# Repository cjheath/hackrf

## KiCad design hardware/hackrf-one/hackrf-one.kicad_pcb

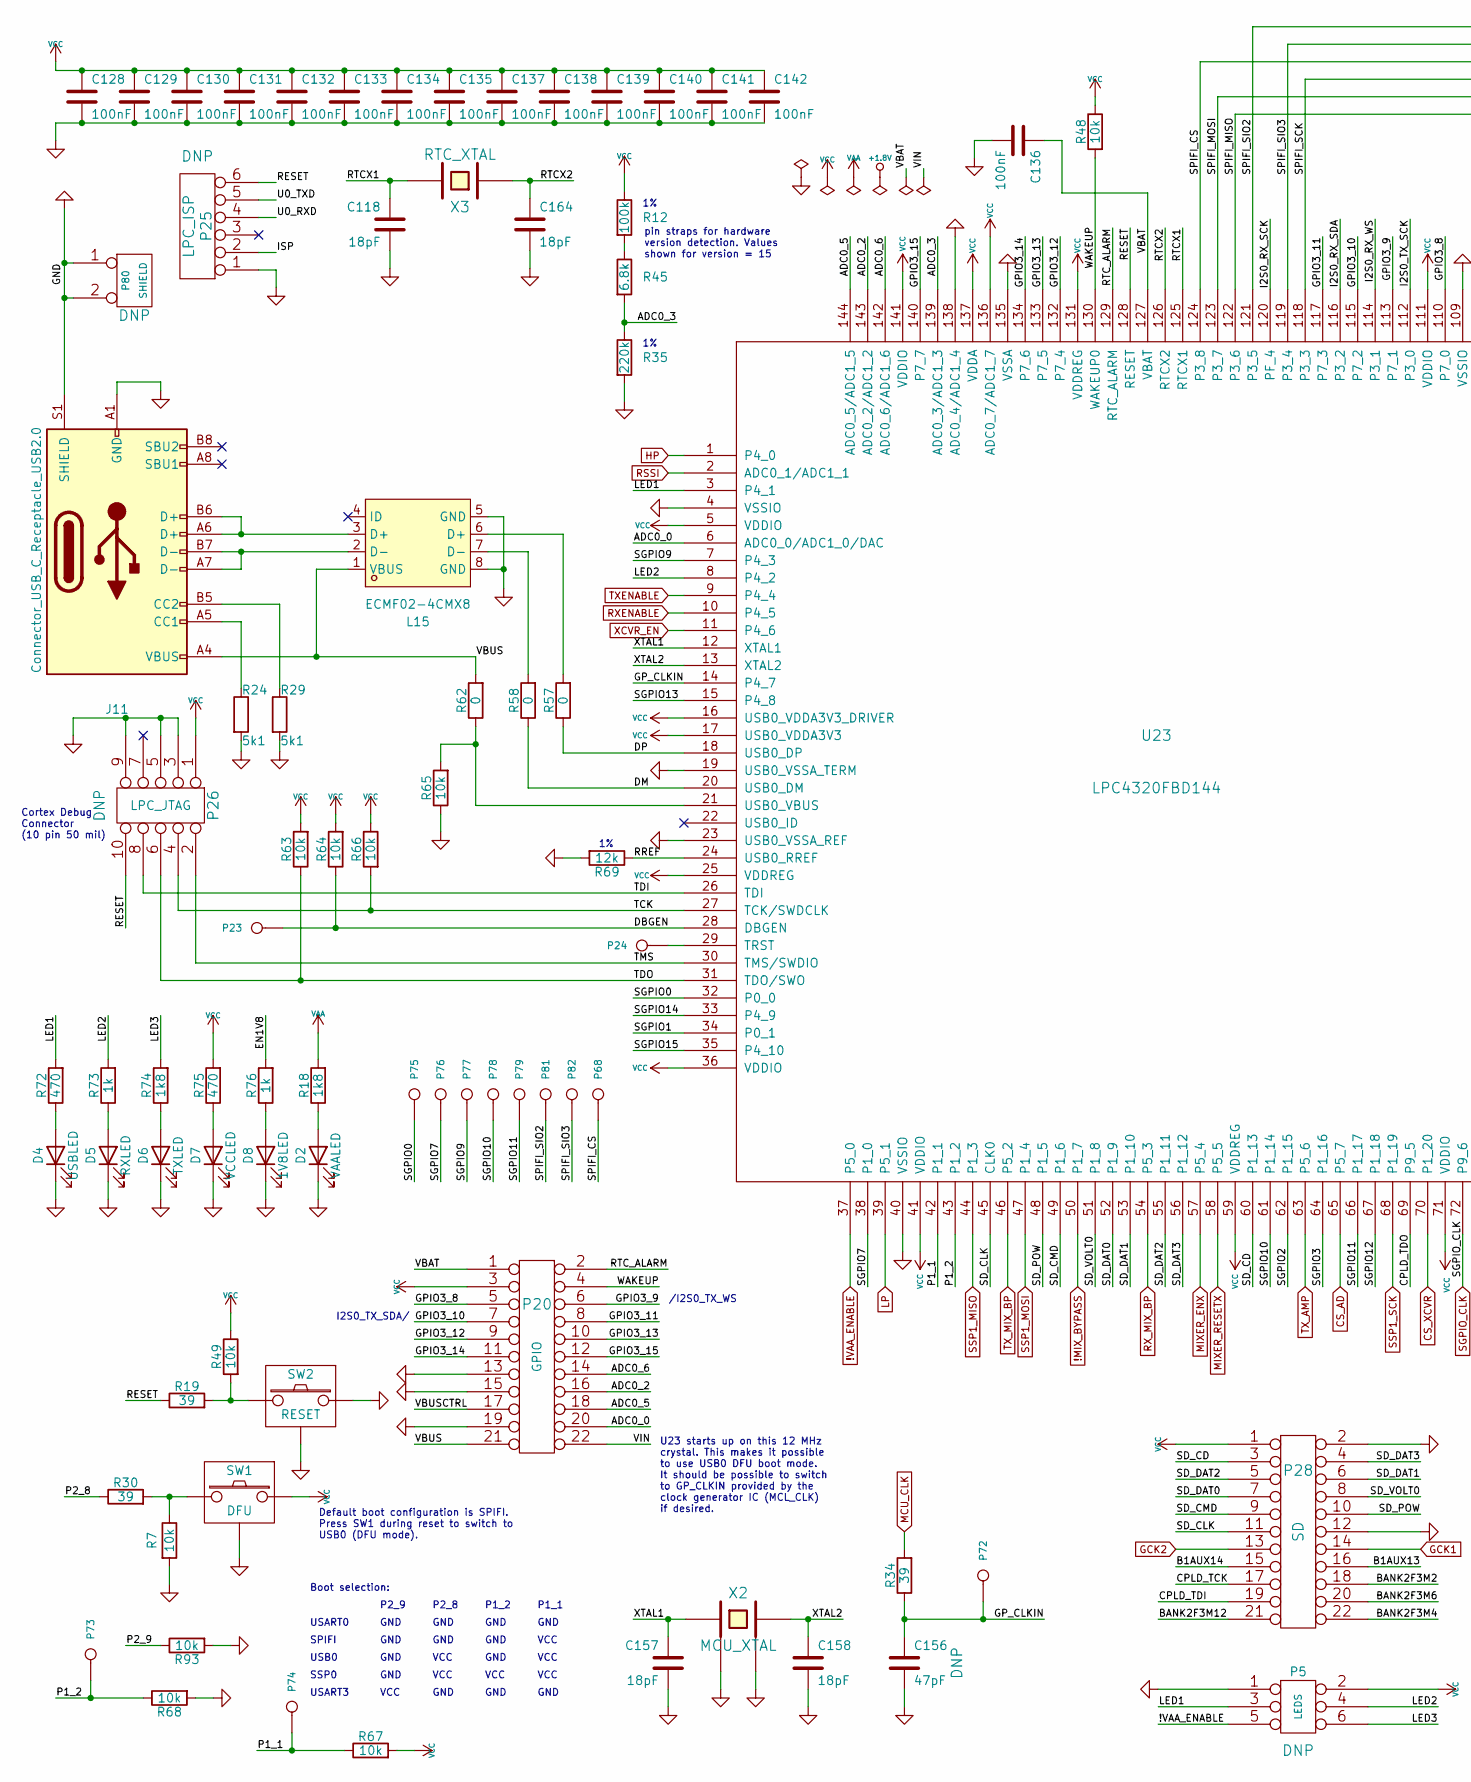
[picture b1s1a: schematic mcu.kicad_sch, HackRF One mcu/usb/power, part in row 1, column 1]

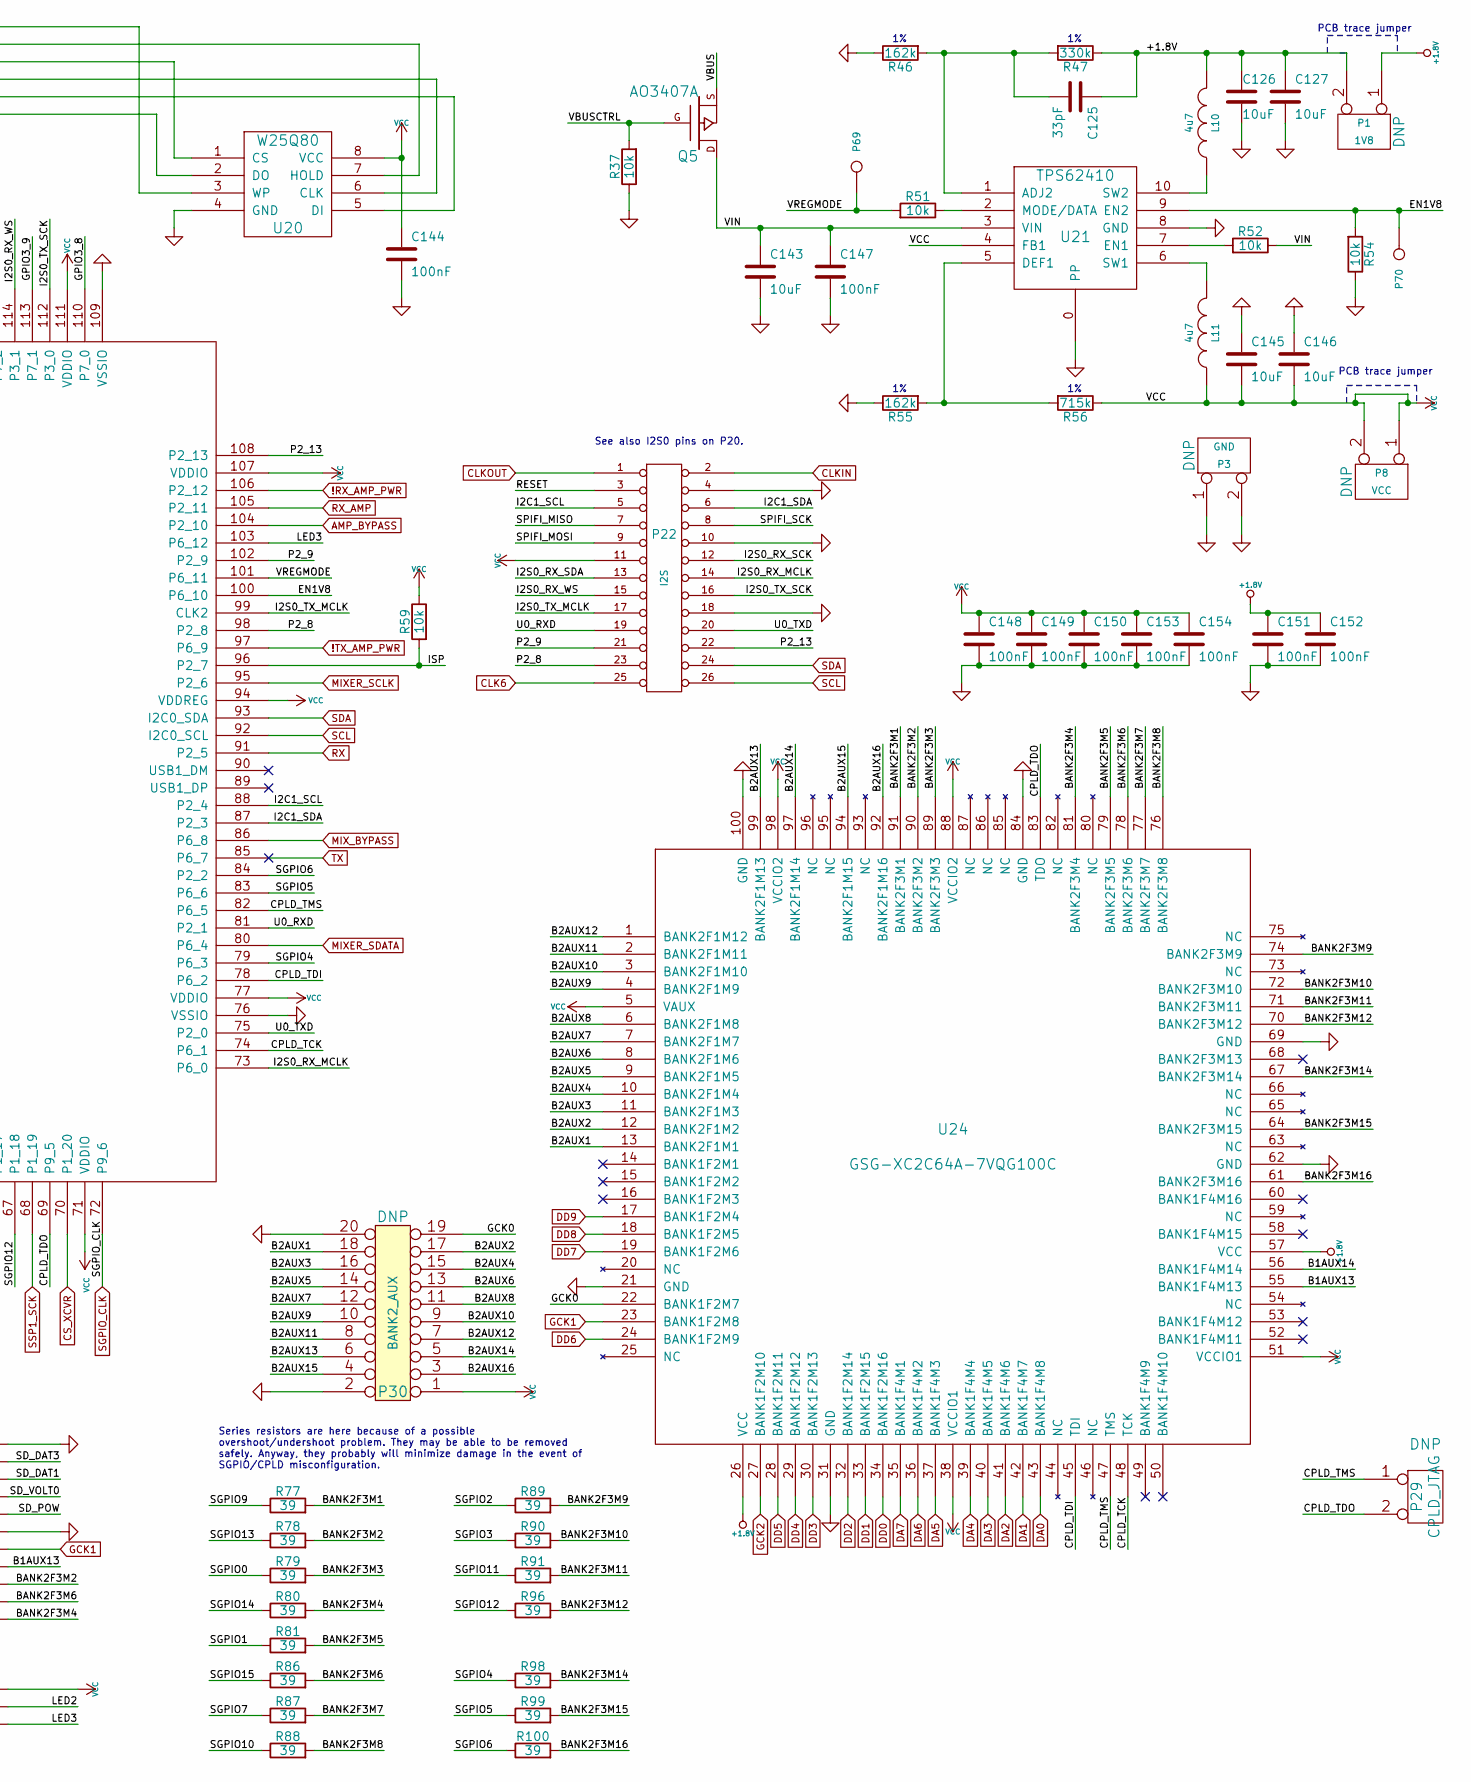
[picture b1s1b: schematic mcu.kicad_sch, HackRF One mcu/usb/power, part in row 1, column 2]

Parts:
C118, C157, C158, C164: 18pF; GSG-0402; Part Number GRM1555C1H180JA01D
C125: 33pF; GSG-0402; Part Number GRM1555C1H330JA01D
C126, C127, C143, C145, C146: 10uF; GSG-0805; Part Number GRM21BR61A106KE19L
C128, C129, C130, C131, C132, C133, C134, C135, C136, C137, C138, C139, C140, C141, C142, C144, C147, C148, C149, C150, C151, C152, C153, C154: 100nF; GSG-0402; Part Number GRM155R61A104KA01D
C156: 47pF; GSG-0402; Part Number GRM1555C1H470JA01D
D2: VAALED; LTST-S220; Part Number LTST-S220KRKT
D4: USBLED; LTST-S220; Part Number LTST-S220KGKT
D5: RXLED; LTST-S220; Part Number LTST-S220KSKT
D6: TXLED; LTST-S220; Part Number LTST-S220KRKT
D7: VCCLED; LTST-S220; Part Number LTST-S220KGKT
D8: 1V8LED; LTST-S220; Part Number LTST-S220KSKT
J11: Connector_USB_C_Receptacle_USB2.0; USB-C_SMD-TYPE-C-31-M-12
L10, L11: 4u7; GSG-NRG4026; Part Number NRG4026T4R7M
L15: ECMF02-4CMX8; QFN-8_L2.5-W1.2-P0.50-BL; LCSC Part C717678
P1: 1V8; GSG-HEADER-1x2
P3: GND; GSG-HEADER-NOMARK-1x2
P5: LEDS; GSG-HEADER-2x3
P8: VCC; GSG-HEADER-1x2
P20: GPIO; GSG-HEADER-2x11; Part Number PPPC112LFBN-RC
P22: I2S; GSG-HEADER-2x13; Part Number PPPC132LFBN-RC
P23: DBGEN; GSG-TESTPOINT-50MIL
P24: TRST; GSG-TESTPOINT-50MIL
P25: LPC_ISP; GSG-HEADER-1x6
P26: LPC_JTAG; GSG-50MIL-HEADER-2x5-TH; Part Number GRPB052VWVN-RC
P28: SD; GSG-HEADER-2x11; Part Number PPPC112LFBN-RC
P29: CPLD_JTAG; GSG-HEADER-1x2
P30: BANK2_AUX; GSG-HEADER-2x10
P68: SPIFI_CS; GSG-TESTPOINT-50MIL
P69: VREGMODE; GSG-TESTPOINT-50MIL
P70: EN_1V8; GSG-TESTPOINT-50MIL
P72, P75, P76, P77, P78, P79: GP_CLKIN; GSG-TESTPOINT-50MIL
P73: P1_2; GSG-TESTPOINT-50MIL
P74: P1_1; GSG-TESTPOINT-50MIL
P80: SHIELD; GSG-HEADER-NOMARK-1x2
P81: SPIFI_SIO2; GSG-TESTPOINT-50MIL
P82: SPIFI_SIO3; GSG-TESTPOINT-50MIL
Q5: AO3407A; SOT23GDS; Part Number AO3407A
R7, R37, R48, R49, R51, R52, R54, R59, R63, R64, R65, R66, R67, R68, R93: 10k; GSG-0402; Part Number RMCF0402JT10K0
R12: 100k; GSG-0402; Part Number RC0402FR-0715K4L
R18, R74: 1k8; GSG-0402; Part Number RMCF0402JT1K80
R19, R30, R34, R77, R78, R79, R80, R81, R86, R87, R88, R89, R90, R91, R96, R98, R99, R100: 39; GSG-0402; Part Number RMCF0402JT39R0
R24, R29: 5k1; GSG-0402
R35: 220k; GSG-0402; Part Number RMCF0402FT330K
R45: 6.8k; GSG-0402; Part Number RC0402FR-0715K4L
R46, R55: 162k; GSG-0402; Part Number RMCF0402FT162K
R47: 330k; GSG-0402; Part Number RMCF0402FT330K
R56: 715k; GSG-0402; Part Number RMCF0402FT715K
R57, R58, R62: 0; GSG-0402; Part Number RMCF0402ZT0R00
R69: 12k; GSG-0402; Part Number MCR01MRTF1202
R72, R75: 470; GSG-0402; Part Number RMCF0402JT470R
R73, R76: 1k; GSG-0402; Part Number RMCF0402FT1K00
SW1: DFU; GSG-SWITCH-FSMRA; Part Number FSMRA3JH
SW2: RESET; GSG-SWITCH-FSMRA; Part Number FSMRA3JH
U20: W25Q80; GSG-SOIC8-208; Part Number W25Q80DVSSIG
U21: TPS62410; GSG-S-PVSON-N10; Part Number TPS62410DRCR
U23: LPC4320FBD144; GSG-LQFP144; Part Number LPC4320FBD144,551
U24: GSG-XC2C64A-7VQG100C; GSG-VQ100; Part Number XC2C64A-7VQG100C
X2: MCU_XTAL; GSG-XTAL3.2x2.5mm; Part Number 7V-12.000MAAE-T
X3: RTC_XTAL; GSG-XTAL-AB26TRQ; Part Number AB26TRQ-32.768KHZ-T

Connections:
!MIX_BYPASS: U23.50 (P1_7); also elsewhere on the board
!RX_AMP_PWR: U23.106 (P2_12); also elsewhere on the board
!TX_AMP_PWR: U23.97 (P6_9); also elsewhere on the board
!VAA_ENABLE: P5.5, U23.37 (P5_0); also elsewhere on the board
+1.8V: C125.1, C126.1, C127.1, C151.1, C152.1, L10.2, P1.1, P1.2 (PM), R47.1, U24.26 (VCC), U24.57 (VCC)
/mcu/usb/power/ADC0_0: P20.20, U23.6 (ADC0_0/ADC1_0/DAC)
/mcu/usb/power/ADC0_2: P20.16, U23.143 (ADC0_2/ADC1_2)
/mcu/usb/power/ADC0_3: R35.1, R45.2, U23.139 (ADC0_3/ADC1_3)
/mcu/usb/power/ADC0_5: P20.18, U23.144 (ADC0_5/ADC1_5)
/mcu/usb/power/ADC0_6: P20.14, U23.142 (ADC0_6/ADC1_6)
/mcu/usb/power/B1AUX13: P28.16, U24.55 (BANK1F4M13)
/mcu/usb/power/B1AUX14: P28.15, U24.56 (BANK1F4M14)
/mcu/usb/power/B2AUX1: P30.18, U24.13 (BANK2F1M1)
/mcu/usb/power/B2AUX2: P30.17, U24.12 (BANK2F1M2)
/mcu/usb/power/B2AUX3: P30.16, U24.11 (BANK2F1M3)
/mcu/usb/power/B2AUX4: P30.15, U24.10 (BANK2F1M4)
/mcu/usb/power/B2AUX5: P30.14, U24.9 (BANK2F1M5)
/mcu/usb/power/B2AUX6: P30.13, U24.8 (BANK2F1M6)
/mcu/usb/power/B2AUX7: P30.12, U24.7 (BANK2F1M7)
/mcu/usb/power/B2AUX8: P30.11, U24.6 (BANK2F1M8)
/mcu/usb/power/B2AUX9: P30.10, U24.4 (BANK2F1M9)
/mcu/usb/power/B2AUX10: P30.9, U24.3 (BANK2F1M10)
/mcu/usb/power/B2AUX11: P30.8, U24.2 (BANK2F1M11)
/mcu/usb/power/B2AUX12: P30.7, U24.1 (BANK2F1M12)
/mcu/usb/power/B2AUX13: P30.6, U24.99 (BANK2F1M13)
/mcu/usb/power/B2AUX14: P30.5, U24.97 (BANK2F1M14)
/mcu/usb/power/B2AUX15: P30.4, U24.94 (BANK2F1M15)
/mcu/usb/power/B2AUX16: P30.3, U24.92 (BANK2F1M16)
/mcu/usb/power/BANK2F3M1: R77.2, U24.91 (BANK2F3M1)
/mcu/usb/power/BANK2F3M2: P28.18, R78.2, U24.90 (BANK2F3M2)
/mcu/usb/power/BANK2F3M3: R79.2, U24.89 (BANK2F3M3)
/mcu/usb/power/BANK2F3M4: P28.22, R80.2, U24.81 (BANK2F3M4)
/mcu/usb/power/BANK2F3M5: R81.2, U24.79 (BANK2F3M5)
/mcu/usb/power/BANK2F3M6: P28.20, R86.2, U24.78 (BANK2F3M6)
/mcu/usb/power/BANK2F3M7: R87.2, U24.77 (BANK2F3M7)
/mcu/usb/power/BANK2F3M8: R88.2, U24.76 (BANK2F3M8)
/mcu/usb/power/BANK2F3M9: R89.2, U24.74 (BANK2F3M9)
/mcu/usb/power/BANK2F3M10: R90.2, U24.72 (BANK2F3M10)
/mcu/usb/power/BANK2F3M11: R91.2, U24.71 (BANK2F3M11)
/mcu/usb/power/BANK2F3M12: P28.21, R96.2, U24.70 (BANK2F3M12)
/mcu/usb/power/BANK2F3M14: R98.2, U24.67 (BANK2F3M14)
/mcu/usb/power/BANK2F3M15: R99.2, U24.64 (BANK2F3M15)
/mcu/usb/power/BANK2F3M16: R100.2, U24.61 (BANK2F3M16)
/mcu/usb/power/CPLD_TCK: P28.17, U23.74 (P6_1), U24.48 (TCK)
/mcu/usb/power/CPLD_TDI: P28.19, U23.78 (P6_2), U24.45 (TDI)
/mcu/usb/power/CPLD_TDO: P29.2 (PM), U23.69 (P9_5), U24.83 (TDO)
/mcu/usb/power/CPLD_TMS: P29.1, U23.82 (P6_5), U24.47 (TMS)
/mcu/usb/power/DBGEN: P23.1, R64.1, U23.28 (DBGEN)
/mcu/usb/power/DM: R58.1, U23.20 (USB0_DM)
/mcu/usb/power/DP: R57.1, U23.18 (USB0_DP)
/mcu/usb/power/EN1V8: P70.1, R54.2, R76.2, U21.9 (EN2), U23.100 (P6_10)
/mcu/usb/power/GCK0: P30.19, U24.22 (BANK1F2M7)
/mcu/usb/power/GPIO3_8: P20.5, U23.110 (P7_0)
/mcu/usb/power/GPIO3_9: P20.6, U23.113 (P7_1)
/mcu/usb/power/GPIO3_10: P20.7, U23.115 (P7_2)
/mcu/usb/power/GPIO3_11: P20.8, U23.117 (P7_3)
/mcu/usb/power/GPIO3_12: P20.9, U23.132 (P7_4)
/mcu/usb/power/GPIO3_13: P20.10, U23.133 (P7_5)
/mcu/usb/power/GPIO3_14: P20.11, U23.134 (P7_6)
/mcu/usb/power/GPIO3_15: P20.12, U23.140 (P7_7)
/mcu/usb/power/GP_CLKIN: C156.1, P72.1, R34.1, U23.14 (P4_7)
/mcu/usb/power/I2C1_SCL: P22.5, U23.88 (P2_4)
/mcu/usb/power/I2C1_SDA: P22.6, U23.87 (P2_3)
/mcu/usb/power/I2S0_RX_MCLK: P22.14, U23.73 (P6_0)
/mcu/usb/power/I2S0_RX_SCK: P22.12, U23.120 (PF_4)
/mcu/usb/power/I2S0_RX_SDA: P22.13, U23.116 (P3_2)
/mcu/usb/power/I2S0_RX_WS: P22.15, U23.114 (P3_1)
/mcu/usb/power/I2S0_TX_MCLK: P22.17, U23.99 (CLK2)
/mcu/usb/power/I2S0_TX_SCK: P22.16, U23.112 (P3_0)
/mcu/usb/power/ISP: P25.2, R59.2, U23.96 (P2_7)
/mcu/usb/power/LED1: P5.3, R72.2, U23.3 (P4_1)
/mcu/usb/power/LED2: P5.4, R73.2, U23.8 (P4_2)
/mcu/usb/power/LED3: P5.6, R74.2, U23.103 (P6_12)
/mcu/usb/power/P1_1: P74.1, R67.1, U23.42 (P1_1)
/mcu/usb/power/P1_2: P73.1, R68.1, U23.43 (P1_2)
/mcu/usb/power/P2_8: P22.23, R30.1, U23.98 (P2_8)
/mcu/usb/power/P2_9: P22.21, R93.1, U23.102 (P2_9)
/mcu/usb/power/P2_13: P22.22, U23.108 (P2_13)
/mcu/usb/power/RESET: P22.3, P25.6, P26.10, R19.1, U23.128 (RESET)
/mcu/usb/power/RREF: R69.1, U23.24 (USB0_RREF)
/mcu/usb/power/RTCX1: C118.1, U23.125 (RTCX1), X3.2
/mcu/usb/power/RTCX2: C164.1, U23.126 (RTCX2), X3.1
/mcu/usb/power/RTC_ALARM: P20.2, U23.129 (RTC_ALARM)
/mcu/usb/power/SD_CD: P28.3, U23.60 (P1_13)
/mcu/usb/power/SD_CLK: P28.11, U23.45 (CLK0)
/mcu/usb/power/SD_CMD: P28.9, U23.49 (P1_6)
/mcu/usb/power/SD_DAT0: P28.7, U23.52 (P1_9)
/mcu/usb/power/SD_DAT1: P28.6, U23.53 (P1_10)
/mcu/usb/power/SD_DAT2: P28.5, U23.55 (P1_11)
/mcu/usb/power/SD_DAT3: P28.4, U23.56 (P1_12)
/mcu/usb/power/SD_POW: P28.10, U23.48 (P1_5)
/mcu/usb/power/SD_VOLT0: P28.8, U23.51 (P1_8)
/mcu/usb/power/SGPIO0: P75.1, R79.1, U23.32 (P0_0)
/mcu/usb/power/SGPIO1: R81.1, U23.34 (P0_1)
/mcu/usb/power/SGPIO2: R89.1, U23.62 (P1_15)
/mcu/usb/power/SGPIO3: R90.1, U23.64 (P1_16)
/mcu/usb/power/SGPIO4: R98.1, U23.79 (P6_3)
/mcu/usb/power/SGPIO5: R99.1, U23.83 (P6_6)
/mcu/usb/power/SGPIO6: R100.1, U23.84 (P2_2)
/mcu/usb/power/SGPIO7: P76.1, R87.1, U23.38 (P1_0)
/mcu/usb/power/SGPIO9: P77.1, R77.1, U23.7 (P4_3)
/mcu/usb/power/SGPIO10: P78.1, R88.1, U23.61 (P1_14)
/mcu/usb/power/SGPIO11: P79.1, R91.1, U23.66 (P1_17)
/mcu/usb/power/SGPIO12: R96.1, U23.67 (P1_18)
/mcu/usb/power/SGPIO13: R78.1, U23.15 (P4_8)
/mcu/usb/power/SGPIO14: R80.1, U23.33 (P4_9)
/mcu/usb/power/SGPIO15: R86.1, U23.35 (P4_10)
/mcu/usb/power/SPIFI_CS: P68.1, U20.1 (CS), U23.124 (P3_8)
/mcu/usb/power/SPIFI_MISO: P22.7, U20.2 (DO), U23.122 (P3_6)
/mcu/usb/power/SPIFI_MOSI: P22.9, U20.5 (DI), U23.123 (P3_7)
/mcu/usb/power/SPIFI_SCK: P22.8, U20.6 (CLK), U23.118 (P3_3)
/mcu/usb/power/SPIFI_SIO2: P81.1, U20.3 (WP), U23.121 (P3_5)
/mcu/usb/power/SPIFI_SIO3: P82.1, U20.7 (HOLD), U23.119 (P3_4)
/mcu/usb/power/TCK: P26.4, R66.2, U23.27 (TCK/SWDCLK)
/mcu/usb/power/TDI: P26.8, U23.26 (TDI)
/mcu/usb/power/TDO: P26.6, R63.1, U23.31 (TDO/SWO)
/mcu/usb/power/TMS: P26.2, U23.30 (TMS/SWDIO)
/mcu/usb/power/U0_RXD: P22.19, P25.4, U23.81 (P2_1)
/mcu/usb/power/U0_TXD: P22.20, P25.5, U23.75 (P2_0)
/mcu/usb/power/VBAT: C136.1, P20.1, U23.127 (VBAT)
/mcu/usb/power/VBUS: J11.A4 (VBUS), J11.A9 (VBUS), J11.B4 (VBUS), J11.B9 (VBUS), L15.1 (VBUS), P20.21, Q5.S, R62.2
/mcu/usb/power/VBUSCTRL: P20.17, Q5.G, R37.2
/mcu/usb/power/VIN: C143.1, C147.1, P20.22, Q5.D, R52.1, U21.3 (VIN)
/mcu/usb/power/VREGMODE: P69.1, R51.2, U23.101 (P6_11)
/mcu/usb/power/WAKEUP: P20.4, R48.2, U23.130 (WAKEUP0)
/mcu/usb/power/XTAL1: C157.1, U23.12 (XTAL1), X2.1
/mcu/usb/power/XTAL2: C158.1, U23.13 (XTAL2), X2.3
AMP_BYPASS: U23.104 (P2_10); also elsewhere on the board
CLK6: P22.25 (P24); also elsewhere on the board
CLKIN: P22.2; also elsewhere on the board
CLKOUT: P22.1; also elsewhere on the board
CS_AD: U23.65 (P5_7); also elsewhere on the board
CS_XCVR: U23.70 (P1_20); also elsewhere on the board
DA0: U24.43 (BANK1F4M8); also elsewhere on the board
DA1: U24.42 (BANK1F4M7); also elsewhere on the board
DA2: U24.41 (BANK1F4M6); also elsewhere on the board
DA3: U24.40 (BANK1F4M5); also elsewhere on the board
DA4: U24.39 (BANK1F4M4); also elsewhere on the board
DA5: U24.37 (BANK1F4M3); also elsewhere on the board
DA6: U24.36 (BANK1F4M2); also elsewhere on the board
DA7: U24.35 (BANK1F4M1); also elsewhere on the board
DD0: U24.34 (BANK1F2M16); also elsewhere on the board
DD1: U24.33 (BANK1F2M15); also elsewhere on the board
DD2: U24.32 (BANK1F2M14); also elsewhere on the board
DD3: U24.30 (BANK1F2M13); also elsewhere on the board
DD4: U24.29 (BANK1F2M12); also elsewhere on the board
DD5: U24.28 (BANK1F2M11); also elsewhere on the board
DD6: U24.24 (BANK1F2M9); also elsewhere on the board
DD7: U24.19 (BANK1F2M6); also elsewhere on the board
DD8: U24.18 (BANK1F2M5); also elsewhere on the board
DD9: U24.17 (BANK1F2M4); also elsewhere on the board
GCK1: P28.14, U24.23 (BANK1F2M8); also elsewhere on the board
GCK2: P28.13, U24.27 (BANK1F2M10); also elsewhere on the board
GND: C118.2, C126.2, C127.2, C128.2, C129.2, C130.2, C131.2, C132.2, C133.2, C134.2, C135.2, C136.2, C137.2, C138.2, C139.2, C140.2, C141.2, C142.2, C143.2, C144.2, C145.1, C146.1, C147.2, C148.2, C149.2, C150.2, C151.2, C152.2, C153.2, C154.2, C156.2, C157.2, C158.2, C164.2, D2.1 (K), D4.1 (K), D5.1 (K), D6.1 (K), D7.1 (K), D8.1 (K), J11.A1 (GND), J11.A12 (GND), J11.B1 (GND), J11.B12 (GND), J11.S1 (SHIELD), L15.5 (GND), L15.8 (GND), P3.1, P3.2 (PM), P5.1, P20.13, P20.15, P20.19, P22.4, P22.10, P22.18, P25.1, P26.3, P26.5, P26.9, P28.2, P28.12, P30.2, P30.20, P80.1, P80.2 (PM), R7.2, R24.2, R29.2, R35.2, R37.1, R46.1, R54.1, R55.1, R65.1, R68.2, R69.2, R93.2, SW1.0 (SHIELD), SW2.0 (SHIELD), SW2.1, U20.4 (GND), U21.0 (PP), U21.8 (GND), U23.4 (VSSIO), U23.19 (USB0_VSSA_TERM), U23.23 (USB0_VSSA_REF), U23.40 (VSSIO), U23.76 (VSSIO), U23.109 (VSSIO), U23.135 (VSSA), U23.138 (ADC0_4/ADC1_4), U24.21 (GND), U24.31 (GND), U24.62 (GND), U24.69 (GND), U24.84 (GND), U24.100 (GND), X2.2, X2.4; also elsewhere on the board
HP: U23.1 (P4_0); also elsewhere on the board
LP: U23.39 (P5_1); also elsewhere on the board
MCU_CLK: R34.2; also elsewhere on the board
MIXER_ENX: U23.57 (P5_4); also elsewhere on the board
MIXER_RESETX: U23.58 (P5_5); also elsewhere on the board
MIXER_SCLK: U23.95 (P2_6); also elsewhere on the board
MIXER_SDATA: U23.80 (P6_4); also elsewhere on the board
MIX_BYPASS: U23.86 (P6_8); also elsewhere on the board
unnamed: D2.2 (A), R18.1
unnamed: D4.2 (A), R72.1
unnamed: D5.2 (A), R73.1
unnamed: D6.2 (A), R74.1
unnamed: D7.2 (A), R75.1
unnamed: D8.2 (A), R76.1
unnamed: J11.A5 (CC1), R24.1
unnamed: J11.B5 (CC2), R29.1
unnamed: J11.A6 (D+), J11.B6 (D+), L15.3 (D+)
unnamed: J11.A7 (D-), J11.B7 (D-), L15.2 (D-)
unnamed: L15.6 (D+), R57.2
unnamed: L15.7 (D-), R58.2
unnamed: R12.2, R45.1
unnamed: R19.2, R49.2, SW2.2
unnamed: R7.1, R30.2, SW1.2
unnamed: C125.2, R46.2, R47.2, U21.1 (ADJ2)
unnamed: R55.2, R56.2, U21.5 (DEF1)
unnamed: R52.2, U21.7 (EN1)
unnamed: R51.1, U21.2 (MODE/DATA)
unnamed: L11.2, U21.6 (SW1)
unnamed: L10.1, U21.10 (SW2)
unnamed: P24.1, U23.29 (TRST)
unnamed: R62.1, R65.2, U23.21 (USB0_VBUS)
RSSI: U23.2 (ADC0_1/ADC1_1); also elsewhere on the board
RX: U23.91 (P2_5); also elsewhere on the board
RXENABLE: U23.10 (P4_5); also elsewhere on the board
RX_AMP: U23.105 (P2_11); also elsewhere on the board
RX_MIX_BP: U23.54 (P5_3); also elsewhere on the board
SCL: P22.26 (P22), U23.92 (I2C0_SCL); also elsewhere on the board
SDA: P22.24 (P20), U23.93 (I2C0_SDA); also elsewhere on the board
SGPIO_CLK: U23.72 (P9_6); also elsewhere on the board
SSP1_MISO: U23.44 (P1_3); also elsewhere on the board
SSP1_MOSI: U23.47 (P1_4); also elsewhere on the board
SSP1_SCK: U23.68 (P1_19); also elsewhere on the board
TX: U23.85 (P6_7)
TXENABLE: U23.9 (P4_4); also elsewhere on the board
TX_AMP: U23.63 (P5_6); also elsewhere on the board
TX_MIX_BP: U23.46 (P5_2); also elsewhere on the board
VAA: R18.2; also elsewhere on the board
VCC: C128.1, C129.1, C130.1, C131.1, C132.1, C133.1, C134.1, C135.1, C137.1, C138.1, C139.1, C140.1, C141.1, C142.1, C144.1, C145.2, C146.2, C148.1, C149.1, C150.1, C153.1, C154.1, L11.1, P5.2, P8.1, P8.2 (PM), P20.3, P22.11, P26.1, P28.1, P30.1, R12.1, R48.1, R49.1, R56.1, R59.1, R63.2, R64.2, R66.1, R67.2, R75.2, SW1.1, U20.8 (VCC), U21.4 (FB1), U23.5 (VDDIO), U23.16 (USB0_VDDA3V3_DRIVER), U23.17 (USB0_VDDA3V3), U23.25 (VDDREG), U23.36 (VDDIO), U23.41 (VDDIO), U23.59 (VDDREG), U23.71 (VDDIO), U23.77 (VDDIO), U23.94 (VDDREG), U23.107 (VDDIO), U23.111 (VDDIO), U23.131 (VDDREG), U23.136 (ADC0_7/ADC1_7), U23.137 (VDDA), U23.141 (VDDIO), U24.5 (VAUX), U24.38 (VCCIO1), U24.51 (VCCIO1), U24.88 (VCCIO2), U24.98 (VCCIO2); also elsewhere on the board
XCVR_EN: U23.11 (P4_6); also elsewhere on the board

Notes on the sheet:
I2S0_TX_SDA/
GND
VCC
U23 starts up on this 12 MHz crystal. This makes it possible to use USB0 DFU boot mode. It should be possible to switch to GP_CLKIN provided by the clock generator IC (MCL_CLK) if desired.
See also I2S0 pins on P20.
Series resistors are here because of a possible overshoot/undershoot problem. They may be able to be removed safely. Anyway, they probably will minimize damage in the event of SGPIO/CPLD misconfiguration.
P2_9
Default boot configuration is SPIFI. Press SW1 during reset to switch to USB0 (DFU mode).
/I2S0_TX_WS
Cortex Debug Connector (10 pin 50 mil)
P1_2
PCB trace jumper
P1_1
USART0
SPIFI
pin straps for hardware version detection. Values shown for version = 15
P2_8
USB0
SSP0
USART3
Boot selection:

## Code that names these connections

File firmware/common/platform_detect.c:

/*
 * Copyright 2022 Great Scott Gadgets <info@greatscottgadgets.com>
 *
 * This file is part of HackRF.
 *
 * This program is free software; you can redistribute it and/or modify
 * it under the terms of the GNU General Public License as published by
 * the Free Software Foundation; either version 2, or (at your option)
 * any later version.
 *
 * This program is distributed in the hope that it will be useful,
 * but WITHOUT ANY WARRANTY; without even the implied warranty of
 * MERCHANTABILITY or FITNESS FOR A PARTICULAR PURPOSE.  See the
 * GNU General Public License for more details.
 *
 * You should have received a copy of the GNU General Public License
 * along with this program; see the file COPYING.  If not, write to
 * the Free Software Foundation, Inc., 51 Franklin Street,
 * Boston, MA 02110-1301, USA.
 */

#include "platform_detect.h"
#include "firmware_info.h"
#include "gpio_lpc.h"
#include "hackrf_core.h"

#include <libopencm3/lpc43xx/scu.h>
#include <libopencm3/lpc43xx/adc.h>

static board_id_t platform = BOARD_ID_UNDETECTED;
static board_rev_t revision = BOARD_REV_UNDETECTED;

static struct gpio_t gpio2_9_on_P5_0 = GPIO(2, 9);
static struct gpio_t gpio3_6_on_P6_10 = GPIO(3, 6);

#define P5_0_PUP  (1 << 0)
#define P5_0_PDN  (1 << 1)
#define P6_10_PUP (1 << 2)
#define P6_10_PDN (1 << 3)

/*
 * Jawbreaker has a pull-down on P6_10 and nothing on P5_0.
 * rad1o has a pull-down on P6_10 and a pull-down on P5_0.
 * HackRF One OG has a pull-down on P6_10 and a pull-up on P5_0.
 * HackRF One r9 has a pull-up on P6_10 and a pull-down on P5_0.
 */

#define JAWBREAKER_RESISTORS (P6_10_PDN)
#define RAD1O_RESISTORS      (P6_10_PDN | P5_0_PDN)
#define HACKRF1_OG_RESISTORS (P6_10_PDN | P5_0_PUP)
#define HACKRF1_R9_RESISTORS (P6_10_PUP | P5_0_PDN)

/*
 * LEDs are configured so that they flash if the detected hardware platform is
 * not supported by the firmware binary. Only two LEDs are flashed for a
 * hardware detection failure, but three LEDs are flashed if CPLD configuration
 * fails.
 */
static struct gpio_t gpio_led1 = GPIO(2, 1);
static struct gpio_t gpio_led2 = GPIO(2, 2);
static struct gpio_t gpio_led3 = GPIO(2, 8);

/*
 * Return 10-bit ADC result.
 */
uint16_t adc_read(uint8_t pin)
{
	pin &= 0x7;
	uint8_t pin_mask = (1 << pin);
	ADC0_CR = ADC_CR_SEL(pin_mask) | ADC_CR_CLKDIV(45) | ADC_CR_PDN | ADC_CR_START(1);
	while (!(ADC0_GDR & ADC_DR_DONE) || (((ADC0_GDR >> 24) & 0x7) != pin)) {}
	return (ADC0_GDR >> 6) & 0x03FF;
}

void adc_off(void)
{
	ADC0_CR = 0;
}

/*
 * Starting with r6, HackRF One has pin straps on ADC pins that indicate
 * hardware revision. Those pins were unconnected prior to r6, so we test for
 * the unconnected state by averaging several ADC readings.
 */
#define NUM_SAMPLES    (10)
#define LOW_THRESHOLD  (2)
#define HIGH_THRESHOLD (1022)

#define HIGH(x)   ((x) > HIGH_THRESHOLD)
#define LOW(x)    ((x) < LOW_THRESHOLD)
#define ABSENT(x) (((x) >= LOW_THRESHOLD) && ((x) <= HIGH_THRESHOLD))

uint32_t check_pin_strap(uint8_t pin)
{
	int i;
	uint32_t sum = 0;

	for (i = 0; i < NUM_SAMPLES; i++) {
		sum += adc_read(pin);
	}
	adc_off();
	return (sum / NUM_SAMPLES);
}

/*
 * Starting with r10, HackRF One uses a voltage divider on ADC0_3 to set an
 * analog voltage that indicates the hardware revision. The high five bits of
 * the ADC result are mapped to 32 revisions. HackRF One r8 also fits into this
 * scheme with ADC0_3 tied to VCC.
 */
// clang-format off
static const uint8_t revision_from_adc[32] = {
	BOARD_REV_UNRECOGNIZED,
	BOARD_REV_UNRECOGNIZED,
	BOARD_REV_UNRECOGNIZED,
	BOARD_REV_UNRECOGNIZED,
	BOARD_REV_UNRECOGNIZED,
	BOARD_REV_UNRECOGNIZED,
	BOARD_REV_UNRECOGNIZED,
	BOARD_REV_UNRECOGNIZED,
	BOARD_REV_UNRECOGNIZED,
	BOARD_REV_UNRECOGNIZED,
	BOARD_REV_UNRECOGNIZED,
	BOARD_REV_UNRECOGNIZED,
	BOARD_REV_UNRECOGNIZED,
	BOARD_REV_UNRECOGNIZED,
	BOARD_REV_UNRECOGNIZED,
	BOARD_REV_UNRECOGNIZED,
	BOARD_REV_UNRECOGNIZED,
	BOARD_REV_UNRECOGNIZED,
	BOARD_REV_UNRECOGNIZED,
	BOARD_REV_UNRECOGNIZED,
	BOARD_REV_UNRECOGNIZED,
	BOARD_REV_UNRECOGNIZED,
	BOARD_REV_UNRECOGNIZED,
	BOARD_REV_UNRECOGNIZED,
	BOARD_REV_UNRECOGNIZED,
	BOARD_REV_UNRECOGNIZED,
	BOARD_REV_UNRECOGNIZED,
	BOARD_REV_UNRECOGNIZED,
	BOARD_REV_UNRECOGNIZED,
	BOARD_REV_UNRECOGNIZED,
	BOARD_REV_HACKRF1_R10,
	BOARD_REV_HACKRF1_R8
};

// clang-format on

void detect_hardware_platform(void)
{
	uint8_t detected_resistors = 0;

	scu_pinmux(SCU_PINMUX_LED2, SCU_GPIO_NOPULL | SCU_CONF_FUNCTION0);
	scu_pinmux(SCU_PINMUX_LED3, SCU_GPIO_NOPULL | SCU_CONF_FUNCTION0);
	gpio_input(&gpio_led1);
	gpio_output(&gpio_led2);
	gpio_output(&gpio_led3);

	gpio_input(&gpio2_9_on_P5_0);
	gpio_input(&gpio3_6_on_P6_10);

	/* activate internal pull-down */
	scu_pinmux(P5_0, SCU_GPIO_PDN | SCU_CONF_FUNCTION0);
	scu_pinmux(P6_10, SCU_GPIO_PDN | SCU_CONF_FUNCTION0);
	delay_us_at_mhz(4, 96);
	/* tri-state for a moment before testing input */
	scu_pinmux(P5_0, SCU_GPIO_NOPULL | SCU_CONF_FUNCTION0);
	scu_pinmux(P6_10, SCU_GPIO_NOPULL | SCU_CONF_FUNCTION0);
	delay_us_at_mhz(4, 96);
	/* if input rose quickly, there must be an external pull-up */
	detected_resistors |= (gpio_read(&gpio2_9_on_P5_0)) ? P5_0_PUP : 0;
	detected_resistors |= (gpio_read(&gpio3_6_on_P6_10)) ? P6_10_PUP : 0;

	/* activate internal pull-up */
	scu_pinmux(P5_0, SCU_GPIO_PUP | SCU_CONF_FUNCTION0);
	scu_pinmux(P6_10, SCU_GPIO_PUP | SCU_CONF_FUNCTION0);
	delay_us_at_mhz(4, 96);
	/* tri-state for a moment before testing input */
	scu_pinmux(P5_0, SCU_GPIO_NOPULL | SCU_CONF_FUNCTION0);
	scu_pinmux(P6_10, SCU_GPIO_NOPULL | SCU_CONF_FUNCTION0);
	delay_us_at_mhz(4, 96);
	/* if input fell quickly, there must be an external pull-down */
	detected_resistors |= (gpio_read(&gpio2_9_on_P5_0)) ? 0 : P5_0_PDN;
	detected_resistors |= (gpio_read(&gpio3_6_on_P6_10)) ? 0 : P6_10_PDN;

	switch (detected_resistors) {
	case JAWBREAKER_RESISTORS:
		if (!(supported_platform() & PLATFORM_JAWBREAKER)) {
			halt_and_flash(3000000);
		}
		platform = BOARD_ID_JAWBREAKER;
		return;
	case RAD1O_RESISTORS:
		if (!(supported_platform() & PLATFORM_RAD1O)) {
			halt_and_flash(3000000);
		}
		platform = BOARD_ID_RAD1O;
		return;
	case HACKRF1_OG_RESISTORS:
		if (!(supported_platform() & PLATFORM_HACKRF1_OG)) {
			halt_and_flash(3000000);
		}
		platform = BOARD_ID_HACKRF1_OG;
		break;
	case HACKRF1_R9_RESISTORS:
		if (!(supported_platform() & PLATFORM_HACKRF1_R9)) {
			halt_and_flash(3000000);
		}
		platform = BOARD_ID_HACKRF1_R9;
		break;
	default:
		platform = BOARD_ID_UNRECOGNIZED;
		halt_and_flash(1000000);
	}

	uint32_t adc0_3 = check_pin_strap(3);
	uint32_t adc0_4 = check_pin_strap(4);
	uint32_t adc0_7 = check_pin_strap(7);

	if (platform == BOARD_ID_HACKRF1_OG) {
		if (ABSENT(adc0_3) && ABSENT(adc0_4) && ABSENT(adc0_7)) {
			revision = BOARD_REV_HACKRF1_OLD;
		} else if (HIGH(adc0_3) && HIGH(adc0_4)) {
			revision = BOARD_REV_HACKRF1_R6;
		} else if (LOW(adc0_3) && HIGH(adc0_4)) {
			revision = BOARD_REV_HACKRF1_R7;
		} else if (LOW(adc0_4)) {
			adc0_3 >>= 5;
			revision = revision_from_adc[adc0_3];
			if (revision == BOARD_REV_UNRECOGNIZED)
				// Return all six bits of the unrecognised value
				// clang-format off
				revision = (board_rev_t) (BOARD_REV_HACKRF1_ADC_BASE + (adc0_3 & 0x3F));
		} else {
			revision = BOARD_REV_UNRECOGNIZED;
		}
	} else if (platform == BOARD_ID_HACKRF1_R9) {
		if (LOW(adc0_3) && LOW(adc0_4)) {
			revision = BOARD_REV_HACKRF1_R9;
		} else {
			revision = BOARD_REV_UNRECOGNIZED;
		}
	}

	if ((revision > BOARD_REV_HACKRF1_OLD) && LOW(adc0_7)) {
		revision |= BOARD_REV_GSG;
	}
}

board_id_t detected_platform(void)
{
	return platform;
}

board_rev_t detected_revision(void)
{
	return revision;
}

uint32_t supported_platform(void)
{
	return firmware_info.supported_platform;
}

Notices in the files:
hardware/hackrf-one/baseband.kicad_sch:
Copyright 2012-2018 Michael Ossmann
License: GPL v2
hardware/hackrf-one/frontend.kicad_sch:
with improvements Copyright 2020 Clifford Heath.
